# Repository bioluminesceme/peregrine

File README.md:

# Peregrine Split Steno Keyboard 

A wired, split, handwired stenography keyboard with low profile Choc keys (close together to make hitting multiple keys at once easier/more comfortable)

- [ ] (to add, Javelin version photo, green case, when done)

## Keymap layout

This keyboard has the default steno keyboard layout, but to make my life easier I have added 2 extra keys to the left half. This way both halves are symmetrical.
The extra keys are assigned to COPY and PASTE by default.

You can assign this to different keys in keymap.c (replace LCTL(KC_C) and LCTL(KC_V)) and then rebuild the firmware.

```txt
 ┌───┬───┬───┬───┬───┬───┐       ┌───┬───┬───┬───┬───┬───┐
 │CPY│ S │ T │ P │ H │ * │       │ * │ F │ P │ L │ T │ D │
 ├───┼───┼───┼───┼───┼───┤       ├───┼───┼───┼───┼───┼───┤
 │PST│ S │ K │ W │ R │ * │       │ * │ R │ B │ G │ S │ Z │
 └───┴───┴───┼───┼───┼───┤       ├───┼───┼───┴───┴───┴───┘
             │N1 │ A │ O │       │ E │ U │N2 │
             └───┴───┴───┘       └───┴───┴───┘

```

------

# Free files!

All the files are free, and come with beginner-friendly instructions.

You have the option to 

- [handwire](00handwire/HANDWIRE-INSTRUCTIONS.md)
- [use PCBS](00pcbs/PCB-SURFACEMOUNT-INSTRUCTIONS.md)

Handwiring is the cheapest option.

------

# Working on
- [x] Make a proper board in KiCAD (with thanks to the helpers in discord!) 
- [x] boards ordered 
- [x] board tested (and working!)
- [ ] Javelin (wish me luck)

------

# Will I sell this?
- No. I have no plans for a shop.
- I will have spare PCBs that I'm happy to sell so you don't have to order the minimum quantity (2x5) PCBS. If I do, I'll list them here. 
- I may have enough parts to sell a handful of presoldered boards (you add the Choc switches and keycaps). If I do, I'll list them here.
- First come first serve.
- I'm in the Netherlands so shipping might make this option quite expensive for some people compared to ordering them yourself
- Hand wiring is still a good option, and the cheapest way to make one.

# Can you sell this?
- Yes! 
- This repo has everything you need to make your own. 
- Just pay me 10 percent of your profits after the costs of the parts (not labor), for each sale.
- If you create a wireless version please let me add those files and instructions to this repo.

*20% of donations will go to MECFS Research by https://www.omf.ngo*

------

## HELP!

- Sorry, I will not be providing any technical support.

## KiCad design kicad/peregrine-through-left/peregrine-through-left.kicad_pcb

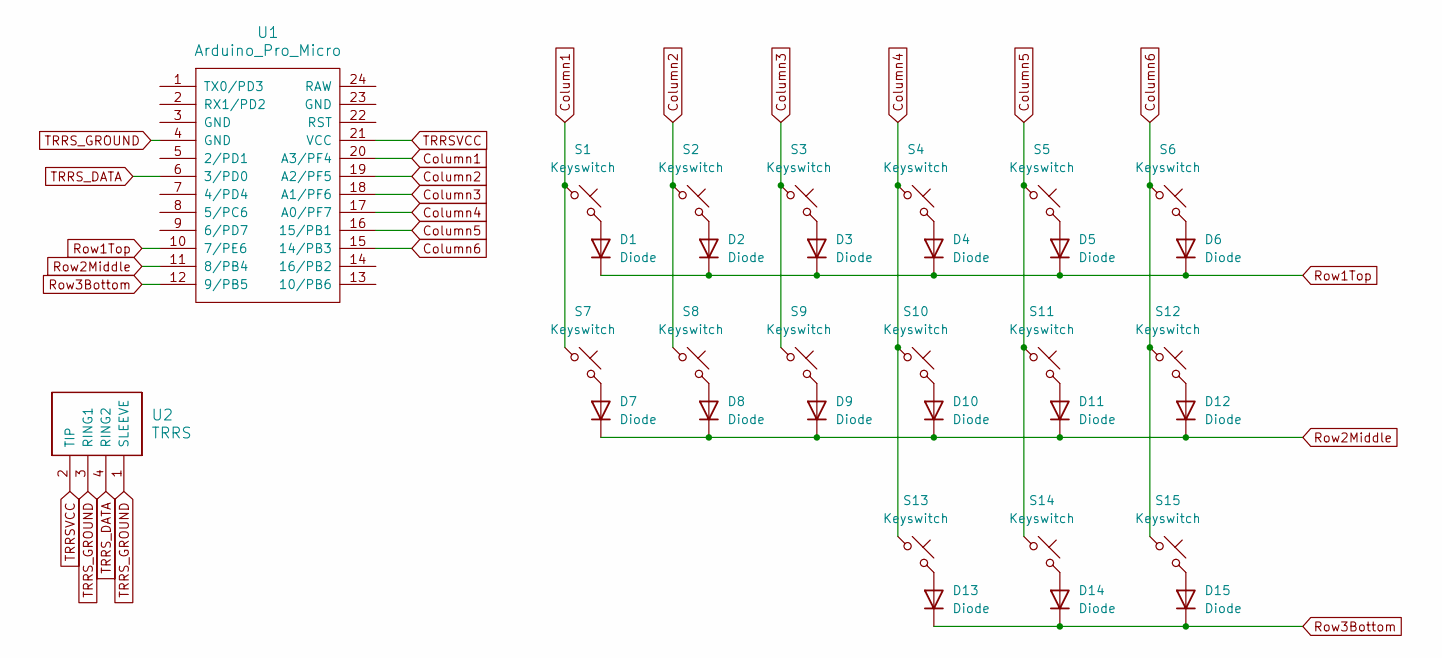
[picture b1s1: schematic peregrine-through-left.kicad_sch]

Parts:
D1, D2, D3, D4, D5, D6, D7, D8, D9, D10, D11, D12, D13, D14, D15: Diode; Diode_DO-35
S1, S2, S3, S4, S5, S6, S7, S8, S9, S10, S11, S12, S13, S14, S15: Keyswitch; Choc_V2_1.00u
U1: Arduino_Pro_Micro
U2: TRRS; TRRS_PJ-320A

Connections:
Column1: S1.1, S7.1, U1.20 (A3/PF4)
Column2: S2.1, S8.1, U1.19 (A2/PF5)
Column3: S3.1, S9.1, U1.18 (A1/PF6)
Column4: S4.1, S10.1, S13.1, U1.17 (A0/PF7)
Column5: S5.1, S11.1, S14.1, U1.16 (15/PB1)
Column6: S6.1, S12.1, S15.1, U1.15 (14/PB3)
unnamed: D1.2 (A), S1.2
unnamed: D2.2 (A), S2.2
unnamed: D3.2 (A), S3.2
unnamed: D4.2 (A), S4.2
unnamed: D5.2 (A), S5.2
unnamed: D6.2 (A), S6.2
unnamed: D7.2 (A), S7.2
unnamed: D8.2 (A), S8.2
unnamed: D9.2 (A), S9.2
unnamed: D10.2 (A), S10.2
unnamed: D11.2 (A), S11.2
unnamed: D12.2 (A), S12.2
unnamed: D13.2 (A), S13.2
unnamed: D14.2 (A), S14.2
unnamed: D15.2 (A), S15.2
Row1Top: D1.1 (K), D2.1 (K), D3.1 (K), D4.1 (K), D5.1 (K), D6.1 (K), U1.10 (7/PE6)
Row2Middle: D7.1 (K), D8.1 (K), D9.1 (K), D10.1 (K), D11.1 (K), D12.1 (K), U1.11 (8/PB4)
Row3Bottom: D13.1 (K), D14.1 (K), D15.1 (K), U1.12 (9/PB5)
TRRSVCC: U1.21 (VCC), U2.2 (TIP)
TRRS_DATA: U1.6 (3/PD0), U2.4 (RING2)
TRRS_GROUND: U1.4 (GND), U2.1 (SLEEVE), U2.3 (RING1)

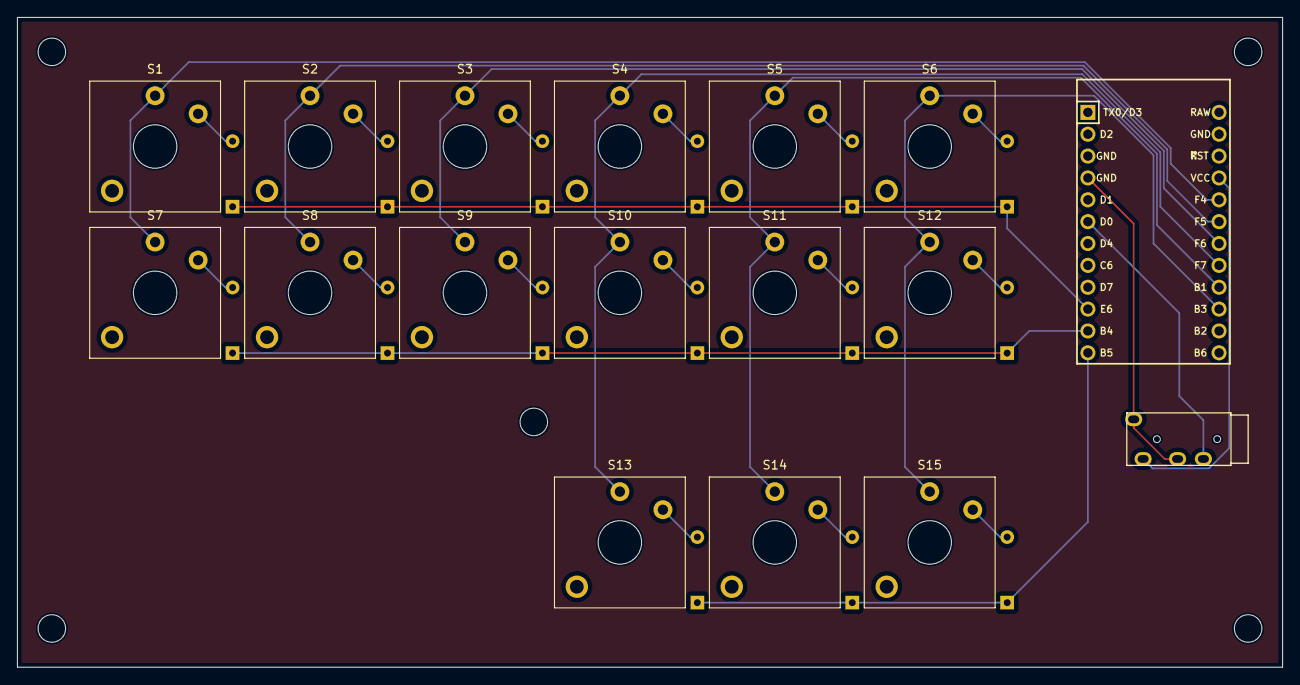
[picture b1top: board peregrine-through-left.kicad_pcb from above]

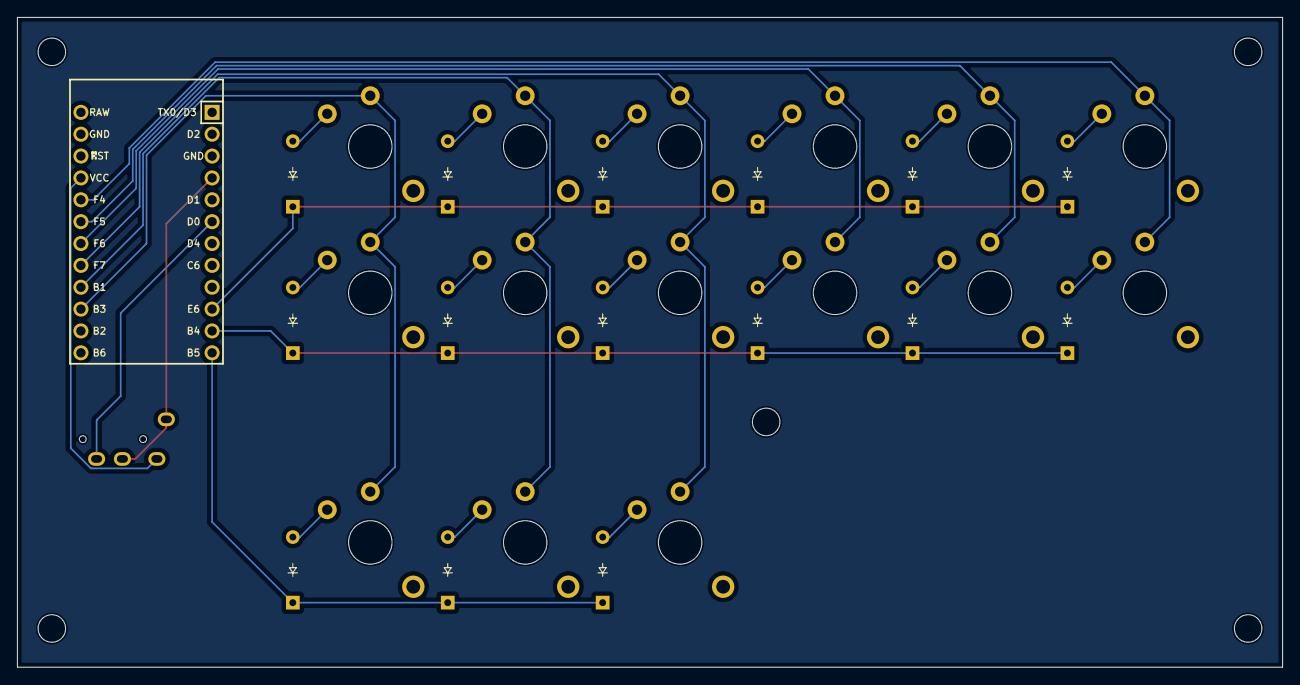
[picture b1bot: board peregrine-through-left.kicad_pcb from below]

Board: 2 copper layers, 147.0 x 75.5 mm, 32 parts (15 on the bottom side), 27 nets.

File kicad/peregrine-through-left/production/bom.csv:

Designator,Footprint,Quantity,Value,LCSC Part #
"D1, D10, D11, D12, D13, D14, D15, D2, D3, D4, D5, D6, D7, D8, D9",Diode_DO-35,15,Diode,
"S1, S10, S11, S12, S13, S14, S15, S2, S3, S4, S5, S6, S7, S8, S9",Choc_V2_1.00u,15,Keyswitch,
U1,Arduino_Pro_Micro,1,Arduino_Pro_Micro,
U2,TRRS_PJ-320A,1,TRRS,

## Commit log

2025-09-26 Initial commit. Peregrine 2025
2025-09-26 Added a photo of Peregrine assembled
2025-09-26 README updated.
2025-09-26 Added a ko-fi button ♥
2025-10-29 Revise ToDo section to Working and Future possibilities
    Updated the README to reflect current plans and future possibilities.
2025-10-29 Fix typos and improve clarity in README
    Corrected typos and clarified instructions in README.
2025-10-31 Added KiCad files for 2 board versions. Surface mount hotswap / through hole Choc switches.
2025-10-31 Added kicad howto, need to improve this later, test boards first.
2025-11-27 Updated ReadMe, added instructions, added 3D case files
2025-11-27 added photo of finished PCB, cleaning up
2025-11-27 cleaning unused files, updating readme
